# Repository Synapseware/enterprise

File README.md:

Enterprise
==========
The Enterprise is a project which adds sound and light effects to a small plastic model USS Enterprise from the original Star Trek TV show.  There are various pieces and parts to make this massively over complicated system work.  For me, this project is about learning better techniques for making circuit boards, programming embedded systems and generally wasting massive amounts of time.

# Project Structure
## /board
This is where the Eagle CAD files reside.  You should use Eagle v7 (or greater) to view/edit.

## /core
The heart of the system, driven by an Atmel ATMega328p micro controller clockec at 20MHz.  This is a hand built system and *does not run any Arduino firmware.*  The core is responsible for playing sound effects and coordinating light effects throughout the ship.

## /eeprom-test
A diagnostic firmware image for tracking down problems with the C++ conversion, hardware issues, etc, that are preventing the EEPROM chips from working correctly.

## /effects
The sound files used to generate the the EEPROM image file, and the latest binary EEPROM image file.  Plus lots of ther other sound effects.

## /entutil
Various programs written in C++ (tested only on Linux), mainly for converting 8bit 8KHz wave files to a standard EEPROM image file for uploading to the core.

## /lib
Shared code, drivers and other utilities extracte from the [libs](https://github.com/Synapseware/libs/libs.git) repository.

## /nacelle
A sub project within the main Enterprise project, the [Nacelle](https://github.com/Synapseware/enterprise/tree/master/nacelle) folder contains all the Atmel assembly language files for the nacelle lighting effects boards.

# Processing
## The core is responsible for:
* Sending new lighting effects to the Nacelle's for storage via EEPROM
* Sound?
* Some lighting effects
* USB interface

## Unsupported functionality:
* Processing battery level
* Uploading new firmware to subordinate processors

## Hardware System Composition
* Main CPU board
  * Main CPU
  * core lighting effects support
  * sound effects & speaker driver
* Power & USB board
  * USB to COM port
  * charging LiPo battery
  * 5V boost/regulator
* Nacelle boards (2 total)
  * nacelle lighting effects

The power & USB board provides communications for the system via a USB to virtual COM port driver chip, as well as a 5V boost/regulator for powering the CPU's.  The board has 6 outputs, 2 for serial RX & TX, USB power, 5V boost, raw battery line and ground.  The connector is meant to mate to the main board so that the main board can receive power and communications lines without the risk of a highly complicated system board.

The main CPU board has a single ATMega328P micro-controller (uC) which drives the sound effects, core lighting effects and is able to communicate with the nacelle driver boards via I2C.

### Board Details

	Power Board pinout (facing up, pins down, L-R)
	1 - RX
	2 - TX
	3 - VBUS
	4 - VBATT
	5 - VBOOST (5V)
	6 - GND

	Nacelle Board pinout (facing up, pins down, L-R)
	1 - MOSI/SDA
	2 - MISO
	3 - SCK/SCL
	4 - Pwr
	5 - GND
	6 = Reset

## Diagnostics
There are 4 LEDs on the main board located near the programming header.  In order from board edge in:
* Heartbeat
* Sound play back
* Serial transfers
* I2C transfers

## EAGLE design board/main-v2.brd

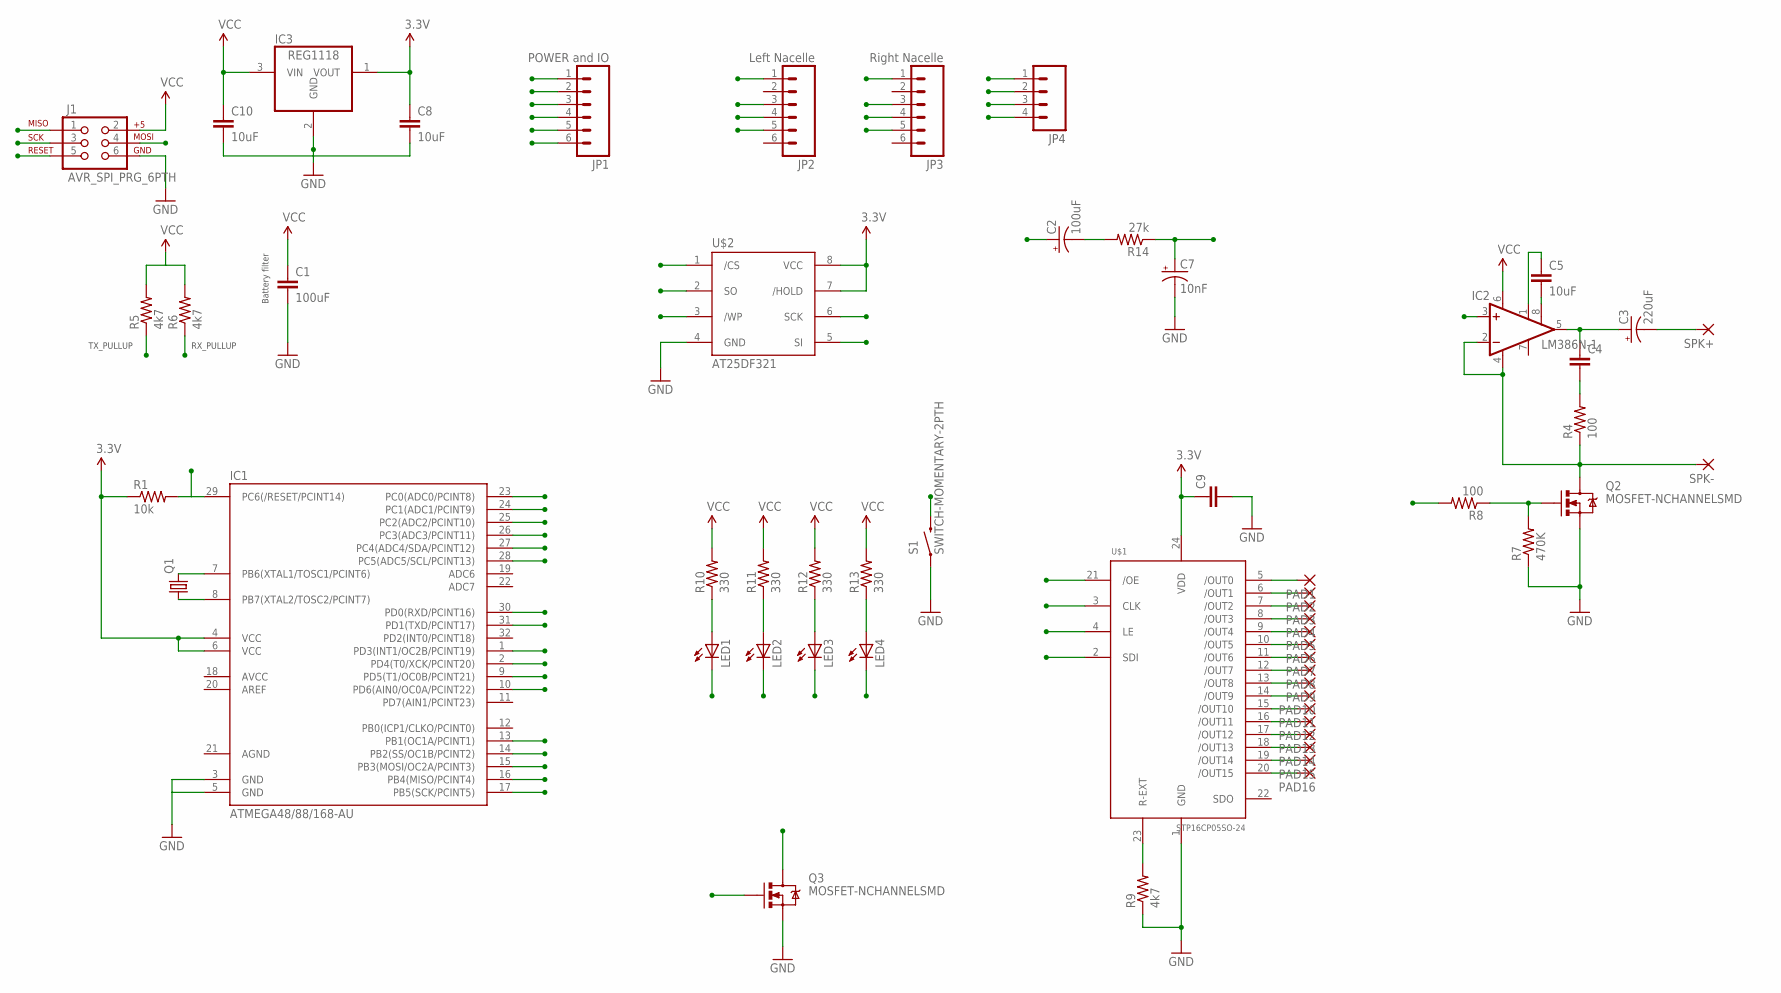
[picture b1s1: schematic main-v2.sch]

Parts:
C1: 100uF; CTZ3
C2: 100uF; CPOL-RADIAL-10UF-25V
C3: 220uF; CPOL-RADIAL-10UF-25V
C4: CAP1206; 1206
C5: 10uF; 1206
C7: 10nF; CPOL-RADIAL-10UF-25V
C8, C10: 10uF; CTZ3
C9: CAP0805; 0805
IC1: ATMEGA48/88/168-AU; TQFP32-08
IC2: LM386N-1; DIL08
IC3: REG1118; SOT223
J1: AVR_SPI_PRG_6PTH; 2X3
JP1: POWER and IO; 1X06
JP2: Left Nacelle; 1X06
JP3: Right Nacelle; 1X06
JP4: M04PTH; 1X04
LED1, LED2, LED3, LED4: LED0603; LED-0603
PAD1, PAD2, PAD3, PAD4, PAD5, PAD6, PAD7, PAD8, PAD9, PAD10, PAD11, PAD12, PAD13, PAD14, PAD15, PAD16: SMD2; SMD1,27-2,54
Q1: CRYSTALCTS406; CTS406
Q2, Q3: MOSFET-NCHANNELSMD; SOT23-3
R1: 10k; 0805
R4, R8: 100; 1206
R5, R6, R9: 4k7; 0805
R7: 470K; 1206
R10, R11, R12, R13: 330; 0805
R14: 27k; 1206
S1: SWITCH-MOMENTARY-2PTH; TACTILE-PTH
SPK+: SMD5; SMD2,54-5,08
SPK-: SMD5; SMD2,54-5,08
U$1: STP16CP05SO-24; SO-24
U$2: AT25DF321; WSOIC-8

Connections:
3.3V: C8.+ (1), C9.1, IC1.4 (VCC), IC1.6 (VCC), IC3.1 (VOUT), R1.1, U$1.24 (VDD), U$2.7 (/HOLD), U$2.8 (VCC)
/OE: IC1.13 (PB1(OC1A/PCINT1)), U$1.21 (/OE)
/SS: IC1.14 (PB2(SS/OC1B/PCINT2)), U$1.4 (LE), U$2.1 (/CS)
AGND: IC1.21 (AGND)
AUDIO_PWR: IC1.2 (PD4(T0/XCK/PCINT20)), R8.2
FILTERED_PWM: C7.1 (+), IC2.3 (+IN), R14.1
GND: C1.- (2), C7.2 (-), C8.- (2), C9.2, C10.- (2), IC1.3 (GND), IC1.5 (GND), IC3.2 (GND), J1.6, JP1.6, JP4.4, Q2.2 (S), Q3.2 (S), R7.1, R9.1, S1.1, U$1.1 (GND), U$2.4 (GND)
LED1: IC1.23 (PC0(ADC0/PCINT8)), LED1.C
LED2: IC1.24 (PC1(ADC1/PCINT9)), LED2.C
LED3: IC1.25 (PC2(ADC2/PCINT10)), LED3.C
LED4: IC1.26 (PC3(ADC3/PCINT11)), LED4.C
MISO: IC1.16 (PB4(MISO/PCINT4)), J1.1, U$2.2 (SO)
MOSI: IC1.15 (PB3(MOSI/OC2A/PCINT3)), J1.4, U$1.2 (SDI), U$2.5 (SI)
unnamed: IC1.8 (PB7(XTAL2/TOSC2/PCINT7)), Q1.1
unnamed: IC1.7 (PB6(XTAL1/TOSC1/PCINT6)), Q1.3 (2)
unnamed: C3.1 (+), C4.1, IC2.5 (OUT)
unnamed: C5.1, IC2.1 (GAIN)
unnamed: C4.2, R4.2
unnamed: C5.2, IC2.8 (GAIN)
unnamed: Q2.1 (G), R7.2, R8.1
unnamed: IC2.2 (-IN), IC2.4 (GND), Q2.3 (D), R4.1, SPK-.1
unnamed: LED1.A, R10.1
unnamed: LED2.A, R11.1
unnamed: R9.2, U$1.23 (R-EXT)
unnamed: LED3.A, R12.1
unnamed: LED4.A, R13.1
unnamed: PAD1.1, U$1.5 (/OUT0)
unnamed: PAD2.1, U$1.6 (/OUT1)
unnamed: PAD3.1, U$1.7 (/OUT2)
unnamed: PAD4.1, U$1.8 (/OUT3)
unnamed: PAD5.1, U$1.9 (/OUT4)
unnamed: PAD6.1, U$1.10 (/OUT5)
unnamed: PAD7.1, U$1.11 (/OUT6)
unnamed: PAD8.1, U$1.12 (/OUT7)
unnamed: PAD9.1, U$1.13 (/OUT8)
unnamed: PAD10.1, U$1.14 (/OUT9)
unnamed: PAD11.1, U$1.15 (/OUT10)
unnamed: PAD12.1, U$1.16 (/OUT11)
unnamed: PAD13.1, U$1.17 (/OUT12)
unnamed: PAD14.1, U$1.18 (/OUT13)
unnamed: PAD15.1, U$1.19 (/OUT14)
unnamed: PAD16.1, U$1.20 (/OUT15)
unnamed: C2.2 (-), R14.2
NCL_GND: JP2.5, JP3.5, Q3.3 (D)
NCL_PWR: IC1.9 (PD5(T1/OC0B/PCINT21)), Q3.1 (G)
PWM_AUDIO: C2.1 (+), IC1.1 (PD3(INT1/OC2B/PCINT19))
PWR_SW: IC1.10 (PD6(AIN0/OC0A/PCINT22)), S1.3 (2)
RESET: IC1.29 (PC6(/RESET/PCINT14)), J1.5, R1.2
RX: IC1.30 (PD0(RXD/PCINT16)), JP1.2, R6.1
SCK: IC1.17 (PB5(SCK/PCINT5)), J1.3, U$1.3 (CLK), U$2.6 (SCK)
SCL: IC1.28 (PC5(ADC5/SCL/PCINT13)), JP2.3, JP3.3, JP4.2
SDA: IC1.27 (PC4(ADC4/SDA/PCINT12)), JP2.1, JP3.1, JP4.1
SPK+: C3.2 (-), SPK+.1
TX: IC1.31 (PD1(TXD/PCINT17)), JP1.1, R5.1
VBATT: C1.+ (1), JP1.5, JP2.4, JP3.4, JP4.3
VBUS: JP1.3
VCC: JP1.4, R5.2, R6.2, R10.2, R11.2, R12.2, R13.2
VCC+5V: C10.+ (1), IC2.6 (VS), IC3.3 (VIN), J1.2

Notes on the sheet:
TX_PULLUP
RX_PULLUP
Battery filter

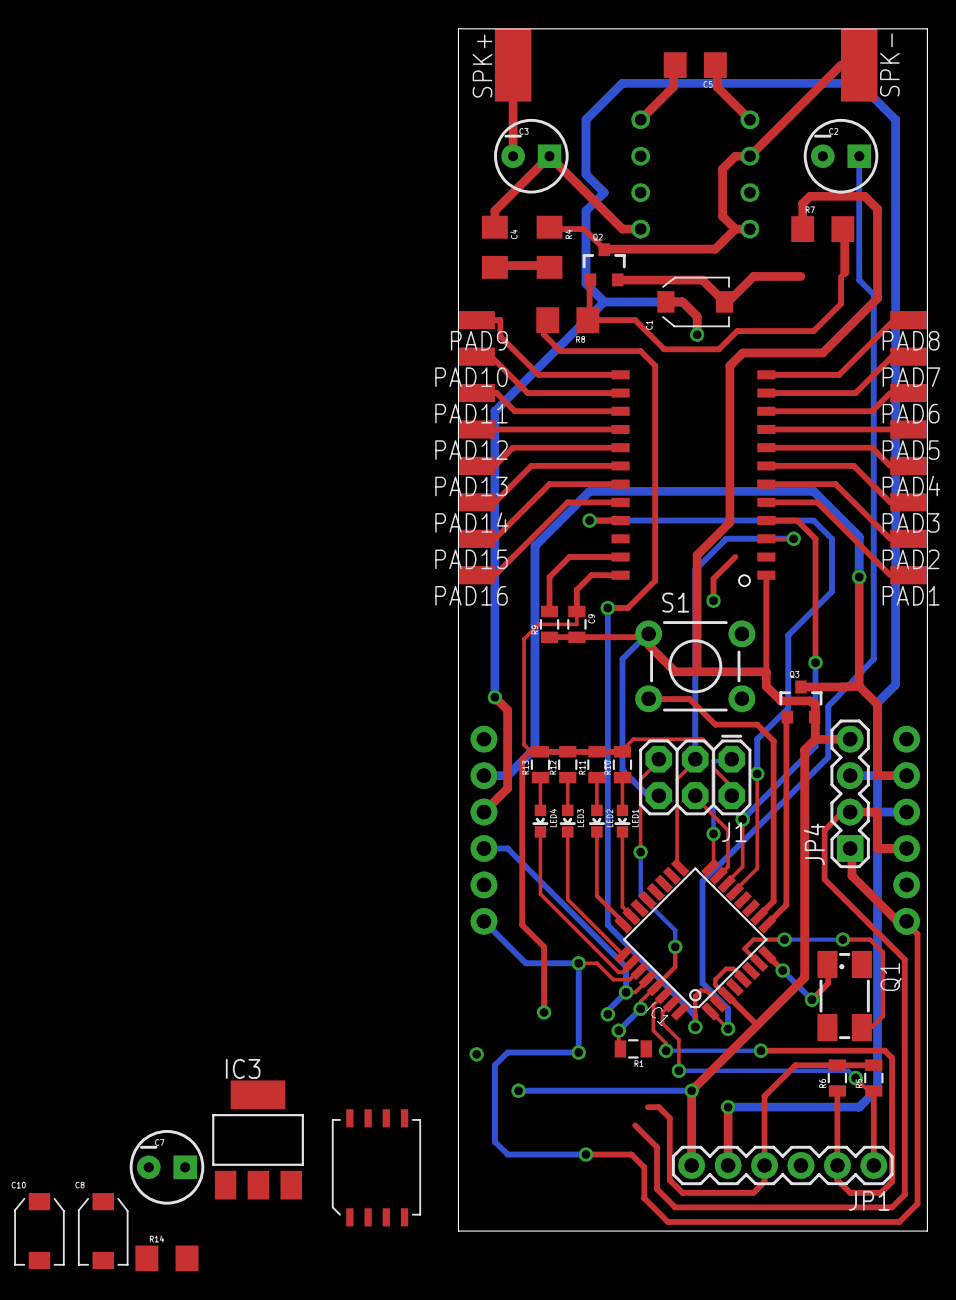
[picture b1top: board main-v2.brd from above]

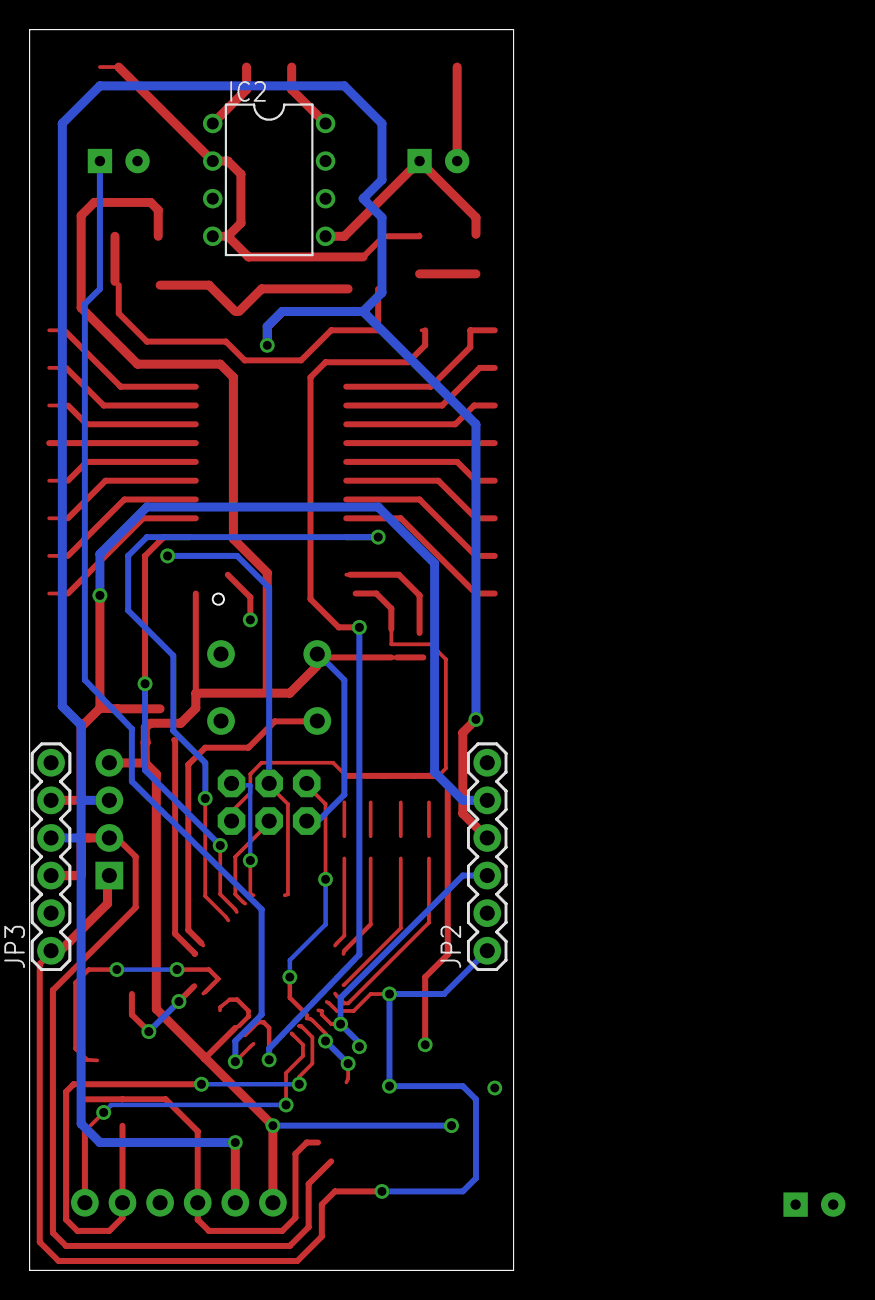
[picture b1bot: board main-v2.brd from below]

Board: 2 copper layers, 32.7 x 83.8 mm, 57 parts (3 on the bottom side), 56 nets.

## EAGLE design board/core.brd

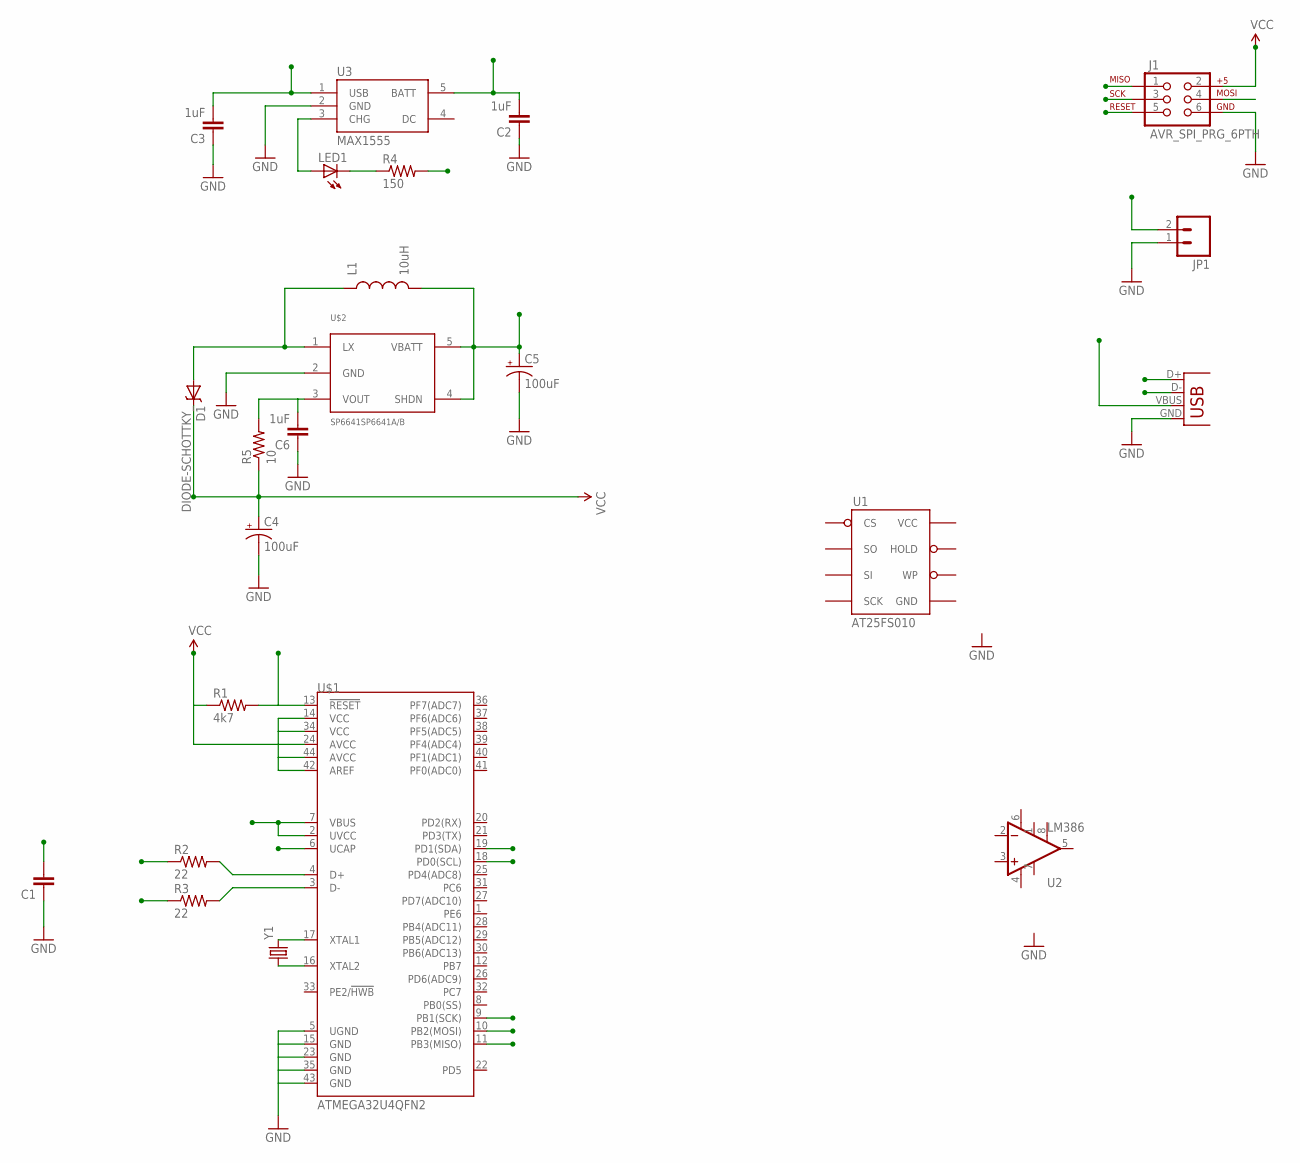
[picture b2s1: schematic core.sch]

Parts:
C1: CAP1206; 1206
C2, C3: 1uF; 1206
C4, C5: 100uF; PANASONIC_E
C6: 1uF; 0603-CAP
D1: DIODE-SCHOTTKY_; SMA-DIODE
J1: AVR_SPI_PRG_6PTH; 2X3
JP1: M02-JST-2MM-SMT; JST-2-SMD
L1: 10uH; CR75
LED1: LED0603; LED-0603
R1: 4k7; 0603-RES
R2, R3: 22; 0603-RES
R4: 150; 0603-RES
R5: 10; 0603-RES
U1: AT25FS010; SO08WIDE
U2: LM386; DIP08
U3: MAX1555; SOT23-5
U$1: ATMEGA32U4QFN2; QFN-44-NOPAD
U$2: SP6641SP6641A/B; SOT23-5
X1: USBSMD; USB-MINIB
Y1: CRYSTAL5X3; CRYSTAL-SMD-5X3

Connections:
/RESET: J1.5, R1.2, U$1.13 (!RESET)
GND: C1.1, C2.1, C3.1, C4.-, C5.-, C6.1, J1.6, JP1.1 (2), U3.2 (GND), U$1.5 (UGND), U$1.15 (GND), U$1.23 (GND), U$1.35 (GND), U$1.43 (GND), U$2.2 (GND), X1.GND
MISO: J1.1, U$1.11 (PB3(MISO))
MOSI: J1.4, U$1.10 (PB2(MOSI))
unnamed: R3.2, U$1.3 (D-)
unnamed: R2.2, U$1.4 (D+)
unnamed: LED1.A, U3.3 (CHG)
unnamed: LED1.C, R4.1
unnamed: D1.A, L1.P$1 (1), U$2.1 (LX)
unnamed: U$1.17 (XTAL1), Y1.3 (2)
unnamed: U$1.16 (XTAL2), Y1.1
unnamed: C6.2, R5.2, U$2.3 (VOUT)
SCK: J1.3, U$1.9 (PB1(SCK))
SCL: U$1.18 (PD0(SCL))
SDA: U$1.19 (PD1(SDA))
UCAP: C1.2, U$1.6 (UCAP)
USB_D+: R2.1, X1.D+
USB_D-: R3.1, X1.D-
V+: U2.6 (V+)
V-: U2.4 (V-)
VBATT: C2.2, C5.+, JP1.2 (1), L1.P$2 (2), U3.5 (BATT), U$2.4 (SHDN), U$2.5 (VBATT)
VBUS: C3.2, R4.2, U3.1 (USB), U$1.2 (UVCC), U$1.7 (VBUS), X1.VBUS
VCC: C4.+, D1.C, J1.2, R1.1, R5.1, U$1.14 (VCC), U$1.24 (AVCC), U$1.34 (VCC), U$1.42 (AREF), U$1.44 (AVCC)

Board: 2 copper layers, 23 parts (0 on the bottom side), 19 nets, no tracks yet.

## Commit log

2014-06-03 Updating makefile and converting to use libs submodule
2014-06-03 Trying to get the make build chain to work...
2014-06-03 Updating makefile - hoping to fix build
2014-06-03 Trying to fix makefile problem again
2014-06-07 Enterprise build now working
2014-06-07 Cleaning up project
2014-06-09 experimenting with new driver files
2014-06-09 Trying to make assembly build work
2014-06-10 Catching up libs submodule
2014-06-11 Nacelle is now building via Assembly build but drivers are not yet converted.
2014-06-11 Updating nacelle build, working on stp16cp05 assembly driver
2014-06-11 Catching up with libs
2014-06-24 Lib sync
2014-06-24 Adding support for new driver files - converting from assembly to C++
2014-06-25 Nacelle now builds using AVRA - sweeeeeet\!
2014-06-25 Updating makefile to be more useful
2014-06-25 Removing experimental source folder
2014-06-25 Updating makefile
2014-06-26 Cleaning up makefile
2014-07-08 Misc updates to Makefile and nacelle
2014-09-13 Updates to sound effects and other minor changes
2014-09-29 getting ready for new event system
2015-04-11 Not sure what these changes are
2015-04-14 Working on Enterprise conversion
2015-04-14 Fixing build issues from migration
2015-04-14 Fixing invokation
2015-04-14 Fixing uart compile error
2015-04-15 Enterprise project is now compiling
2015-04-16 Raw copy of EnterpriseIO project
    A very rough WinForms app which is used to generate the firmware sound effects file.
2015-04-18 Adding console utilities
2015-04-18 Changed converter to infer output file name
2015-04-18 Updates to readme
2015-04-18 Updating platform
2015-04-18 Adding upload command
2015-04-19 Adding upload and header info commandlets
2015-04-20 Updating scvt utility.
2015-04-21 Updates to sound converter
    Changing output extension to .snd from .raw
2015-04-21 Readme changes
2015-04-21 Moving sermem to core project
2015-04-21 WIP - stitch file changes
2015-04-21 Sermem changes and upload improvements
2015-04-21 Changing upload processing
2015-04-21 Added analysis switch
2015-04-22 Working through lots of bugs with UART and Effects
2015-04-22 Catching up libs folder
2015-04-22 Enterprise is now processing serial comms data
2015-04-22 Fixing upload processor and removing command
    Don't commit the compiled upload command
2015-04-22 Reworking the upload processing for the EEPROM
2015-04-23 Did it actually upload?
    Made a few changes to the serial port configuration and the upload processing. Looks like this might actually have uploaded.
2015-04-23 Changing event handling
    Changed event handling and function registration: Moved handlers out of disparete files into the main "Enterprise" file (the one with int main()). Hopefully this fixes some of the callback problems.
2015-04-24 Fix compilation warning
2015-04-24 Misc updates
2015-04-24 Git and makefile updates
    Ignoring build outputs for each project and adding a clean setup.
2015-04-25 Fixing upload processing
    I think the EEPROM wiring is bad on the board... it's not working.
2015-04-25 Updating event registrations and LED calls
2015-04-25 Removing old EnterpriseIO C# project
2015-04-25 Updating the Enterprise documentation
2015-04-26 Small changes to effects events registrations
2015-04-26 Trying to get any serial data to send... :(
2015-04-26 Trying to get serial working (again)
2015-04-26 Working on fixes for the Enterprise
2015-04-27 Adding XModem and more
2015-04-27 Removing old files
2015-04-27 Cleanup
2015-04-28 Trying to fix upload
    * Experimenting with different BAUD rates. So far, 38400 seems to be the most reliable, but it used to transfer @ 115.2k. The board seems to have taken some damage from the move.
    * Transfer size function fixed and correctly reading data from host
    * Upload utility updated for new processing tree
2015-04-28 Adding test program
2015-04-28 Fixing compilation error
2015-04-28 Learning makefile so I can improve my local builds
2015-04-29 Working on XModem usage
2015-04-29 Updating readme to include transfer times
2015-04-29 Fixing compilation error with test program
2015-04-29 Moving test project and refactoring Sermem
2015-04-29 Removing usage of XModem
2015-04-29 Catching up submodule version
2015-04-30 Adding ring buffer support
2015-04-30 Submodule rev
2015-04-30 Ring buffer support and modification for receiving
2015-04-30 Migrating files out of LIBS submodule
    Copied the necessary files to make the Enterprise build without using the damned libs submodule. Going forward, it'll be about integrating changes back to the libs folder as they are made and worth p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
2015-04-30 Adding default Makefile for eeprom test
2015-04-30 Adding EEPROM test project
2015-04-30 Removing libs submodule
2015-04-30 Moving sound effects folder to root
2015-04-30 Renaming libs variable in makefiles
2015-04-30 Improving RingBuffer
2015-05-01 Working on EEPROM test project and UART RingBuffer
2015-05-01 Fixed the TWI interface
    Seems there was a problem with the waiting for-i2c-logic. Fixed and now it's working. Yippie. SO MUCH WASTED TIME. Ugh.
2015-05-01 Cleaning up
2015-05-01 Improving serial transfers and on-board LEDs
2015-05-01 Fixing up UART read's in sermem
2015-05-01 Use scratch buffer instead of function buffers
2015-05-04 Fixing bugs with TWI code
2015-05-04 Changing boundary condition for block read
2015-05-06 Modifying header info utility to show better output
2015-05-06 Sound playing - taking too long to load
    The sound data is playing, but taking far too long to load. Sound effects seem to be playing at 50% or less of their actual speed. Yuck.
2015-05-07 Converting effects class to standard C
2015-05-07 Optimizing
2015-05-07 Minor cleanup
2015-05-08 Adding buffer support to sfx playback
2015-05-08 Fixing load, read and startup
2015-05-08 Reorder methods to remove entries from header
2015-05-08 Fixing LEDs header and implementation
2015-05-08 Call sound render method directly from ISR
2015-05-08 Fixing LEDs header and implementation
    Conflicts:
    core/leds.cpp
    core/leds.h
2015-05-11 Reverting changes from Effects class
    The Effects lib changes accidentally made it to master causing master to be broken. Branch is reverted to last-known good state and Enterprise is playing effects correctly.
2015-05-11 Events and effects timings update
    The Events class was restricting all events to the interval period or less.
2015-05-11 LEDs working and improved read times
2015-05-11 Improved read performance for async reads
    It's more efficient to wait after the start/ack/nack status changes then it is to process the next async step with a callback. This coupled with overclocking the TWI bus @ 800kHz has bought some brea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
2015-05-12 Class conversion
    Why do I keep trying this? I'm hoping that I can use classes with the events class, but alas this leads to really terrible performance, bad design, and likely both.
2017-04-18 Adding playback video
2019-09-23 V2 board files(?)

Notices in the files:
parts and their libraries:
SparkFun-DigitalIC: Licensing: CC v3.0 Share-Alike You are welcome to use this library for commercial purposes.
SparkFun-Aesthetics: Licensing: Creative Commons ShareAlike 4.0 International - https://creativecommons.org/licenses/by-sa/4.0
